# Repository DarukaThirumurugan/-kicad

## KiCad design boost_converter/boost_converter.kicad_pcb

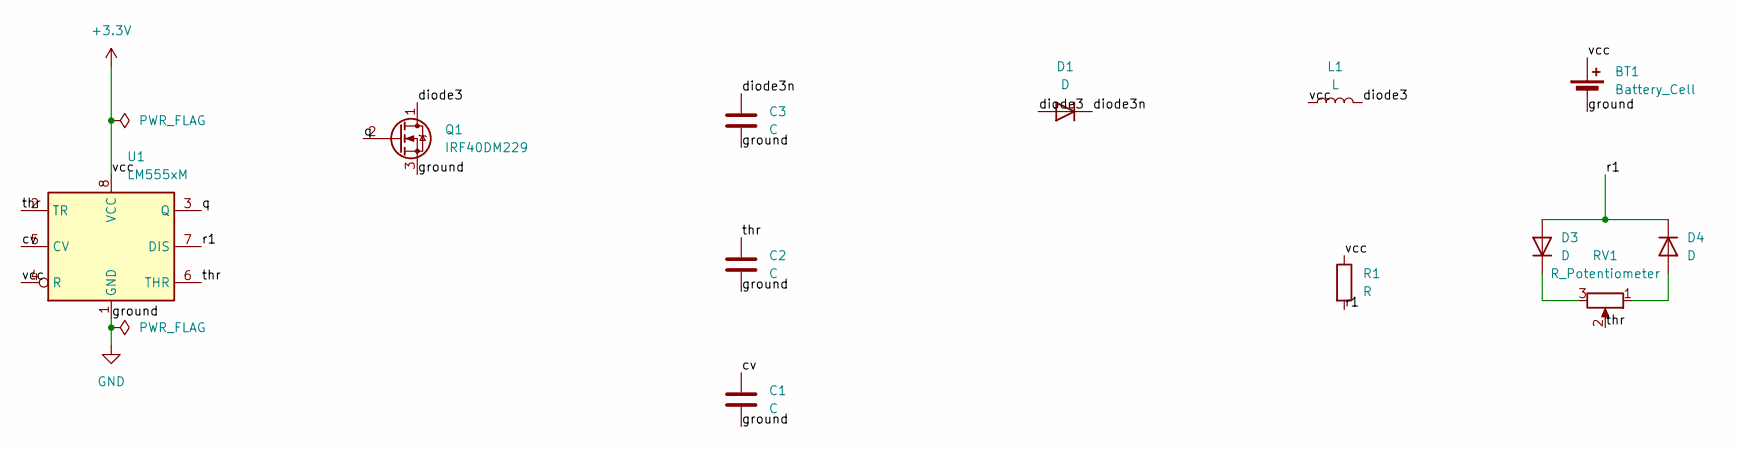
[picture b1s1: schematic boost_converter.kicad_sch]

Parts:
BT1: Battery_Cell; BatteryHolder_Keystone_107_1x23mm
C1, C2, C3: C; C_Axial_L3.8mm_D2.6mm_P15.00mm_Horizontal
D1, D3, D4: D; D_5KP_P10.16mm_Horizontal
L1: L; L_Axial_L16.0mm_D9.5mm_P20.32mm_Horizontal_Vishay_IM-10-37
Q1: IRF40DM229; DirectFET_MF
R1: R; R_0612_1632Metric
RV1: R_Potentiometer; Potentiometer_Piher_PT-15-V15_Vertical_Hole
U1: LM555xM; SOIC-8_3.9x4.9mm_P1.27mm

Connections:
+3.3V: BT1.1 (+), L1.1, R1.1, U1.4 (R), U1.8 (VCC)
/cv: C1.1, U1.5 (CV)
/diode3: D1.2 (A), L1.2, Q1.1 (D)
/diode3n: C3.1, D1.1 (K)
/q: Q1.2 (G), U1.3 (Q)
/r1: D3.2 (A), D4.1 (K), R1.2, U1.7 (DIS)
/thr: C2.1, RV1.2, U1.2 (TR), U1.6 (THR)
GND: BT1.2 (-), C1.2, C2.2, C3.2, Q1.3 (S), U1.1 (GND)
unnamed: D3.1 (K), RV1.3
unnamed: D4.2 (A), RV1.1

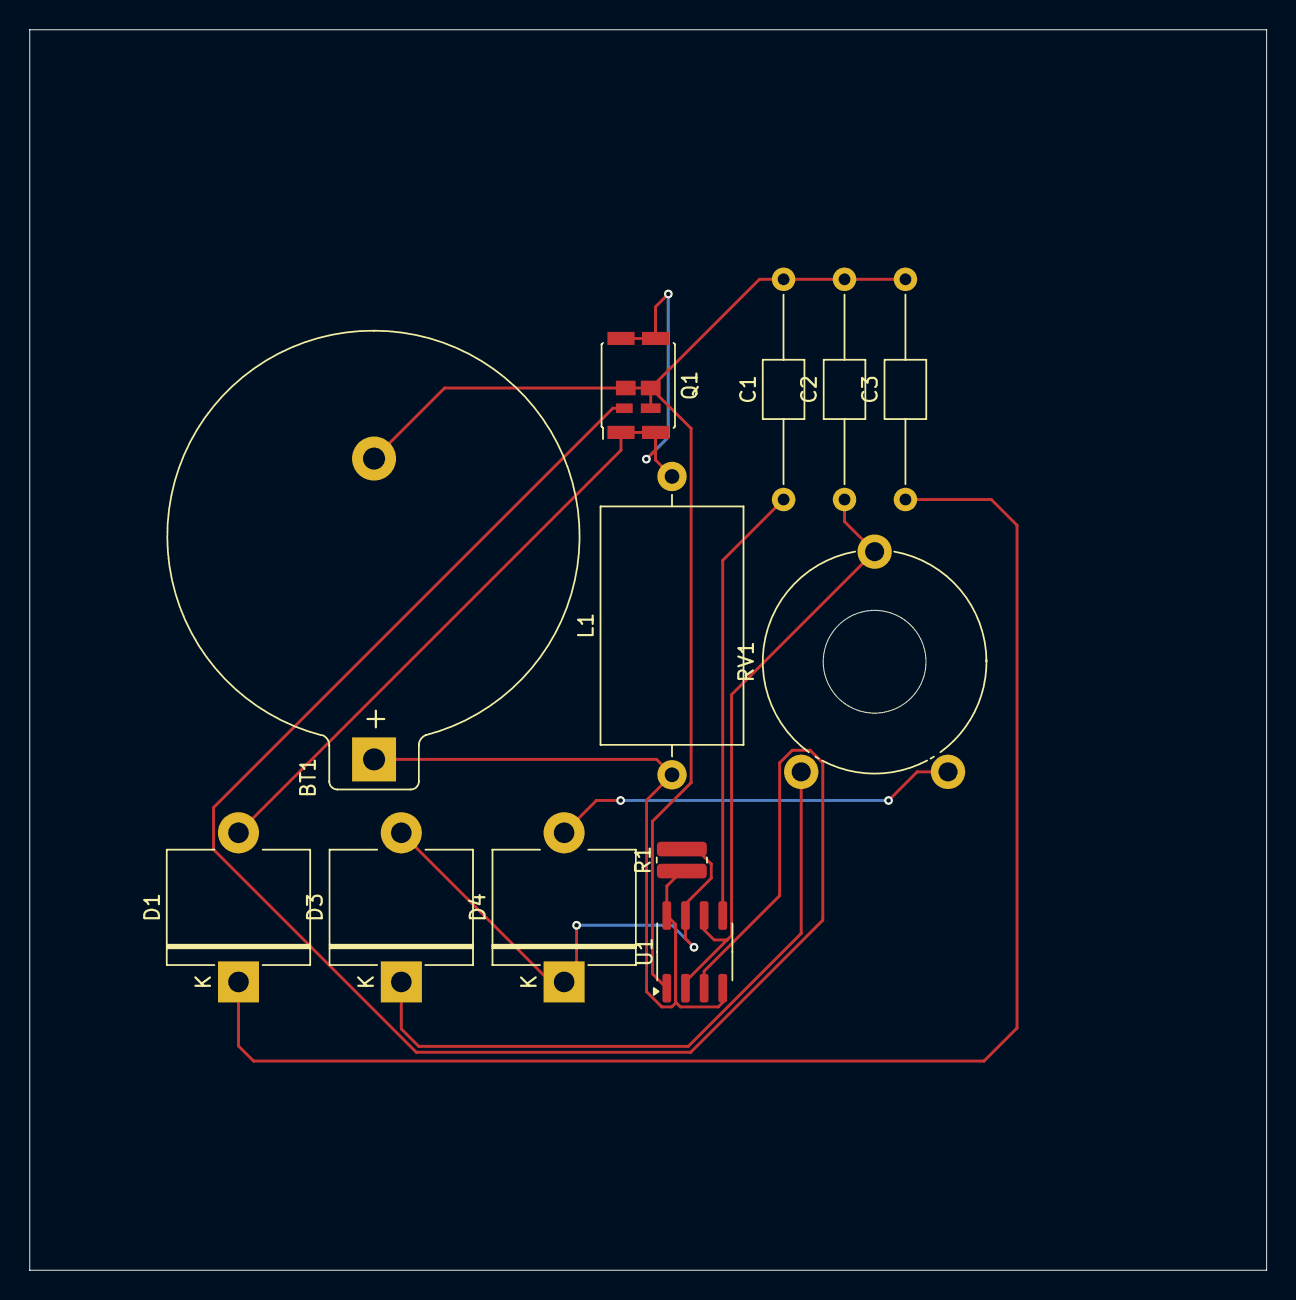
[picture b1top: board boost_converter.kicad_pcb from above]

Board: 2 copper layers, 84.2 x 84.5 mm, 12 parts (0 on the bottom side), 10 nets.

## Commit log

2025-03-20 Kicad buck commit
2025-03-24 boost commit
